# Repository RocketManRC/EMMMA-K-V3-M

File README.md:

# EMMMA-K-V3

# Introduction
The EMMMA-K is a MIDI controller for electronic music that uses touch pins for note keys and user interface. A motion sensor is used to generate MIDI commands for effects such as pitch bend and mod wheel.

The layout of the touch pins for note keys is modeled after the Kalimba (a.k.a. thumb piano) which is a modernized version of the MBira, an ancient African plucked string instrument.

The history and evolution of the MBira and Kalimba is given on Wikipedia here:

[https://en.wikipedia.org/wiki/Mbira](https://en.wikipedia.org/wiki/Mbira)

A great place to see and hear what the Kalimba is all about is April Yang's YouTube channel:

[https://www.youtube.com/channel/UCV0A2VeScCoxiMhsA2kiIKw](https://www.youtube.com/channel/UCV0A2VeScCoxiMhsA2kiIKw)

In January, 2020 I became interested in making an electronic version of the Kalimba because I wanted a keyboard for electronic music that wasn't piano based and also could be hand-held. In March of that year I started working on a proof-of-concept prototype which I called the EMMMA-K. A write-up of that project is on my website here:

[https://www.rocketmanrc.com/emmma-k.html](https://www.rocketmanrc.com/emmma-k.html)

As crude as that first prototype was it actually performed pretty well and so when the COVID-19 lockdown started I decided to spend the time on a second version that had a better shape and layout and would be easier to build. There is also a write-up of that project here:

[https://www.rocketmanrc.com/emmma-k-v2.html](https://www.rocketmanrc.com/emmma-k-v2.html)

This version supported additional music scales in addition to the Kalimba's C Major scale and a user interface was provided to change scale, key and octave.

Fast forward to October 2022... After working on a number of other unrelated projects I started researching what microcontrollers could be used to replace the TeensyLCs I was using that were no longer available due to the dreaded world-wide semiconductor shortage. The primary requirement was touch pin performance meaning good sensitivity and low latency. I discovered that the new ESP32-S2 and ESP32-S3 from Espressif are excellent for this purpose and so the EMMMA-K-V3 was born.

**Videos:**

[https://vimeo.com/858654116](https://vimeo.com/858654116) Introduction

[https://vimeo.com/858421865](https://vimeo.com/858421865) Overview of Features

[https://vimeo.com/858731197](https://vimeo.com/858731197) Under the Hood

# Features

- Kalimba style keyboard with highly responsive and low latency touch pins.
- USB-C connector for USB MIDI and/or power.
- Wireless MIDI over BLE (Bluetooth Low Energy) or ESP-Now wireless to a USB MIDI hub or a Serial MIDI hub.
- ESP-Now wireless is ultra low latency (approximately 1.5 milliseconds).
- Dedicated option touch pin on the right side to enable tilt sensor for pitch bend and mod wheel (or other CC command).
- Multipurpose option touch pin on the left side for switching between major and minor relative scales, changing to chord mode and disabling the adjacent pin and dissonant note filters.
- User interface with OLED display and dedicated touch pins.
- Change Octave, Key and Scale on the fly or display notes as played.
- Settings mode to enable or disable filters, change MIDI channel, set master volume, set CC for mod wheel and choose wireless mode.

# System Design

This is a dual microcontroller master/slave system with a ESP32-S3 used for the master and a ESP32-S2 (or S3) for the slave. Each microcontroller has 14 touch pins and the ESP32-S3 is required for the master to support wireless over BLE (the ESP32-S2 does not). The microcontrollers exchange pin data via a UART connection with the master polling the slave for synchronous communications. The baud rate is set to 2000000 baud to eliminate any noticable latency.

The motion sensor is a breakout board with a MPU-6050 IMU and is connected to the master via I2C. The board provides three absolute angle measurments (roll, pitch and yaw) using the internal processing of the MPU-6050. The roll axis is used for the mod wheel and the pitch axis is used for pitch bend. The yaw axis is not currently used but could be used for some other purpose.

The use of the motion sensor to generate effects is enabled by touching and holding the option pin on the right hand side of the enclosure. This does not require a note to be played which has the advantage of allowing the EMMMA-K to be used for effects along with another MIDI controller. It also has the advantage that the effects will still be applied to a note with sustain even if the noteoff MIDI command has been issued. When the option pin is touched centre angles are calculated for roll and pitch and then the effects are calculated relative to that those. The logic can be changed so that absolute angles are used which works just as well and is a matter of personal preference. Generation of the effects uses a concept from model aviation called "expo". This means that the change in value of the effects are reduced around around the centre position giving a much smoother response overall.

A OLED display of resolution of 128 by 64 pixels is used for the user interface along with three dedicated touch pins. This display is on a seperate I2C port.

Power for the system is provided by a USB connection to a USB power pack or computer USB port.

To minimize point to point wiring PCBs have been designed to carry both the Master and Slave microcontroller boards.

The microcontroller boards are the ESP32-S3-DevKitC-1 and ESP32-S2-DevKitC-1 from Espressif and are available from all the major component suppliers. Alternatively there are versions of the S3 dev board available from AliExpress.

The code for the slave processor (inspite of what Github says in the repository list and pins) is located here:

[https://github.com/RocketManRC/EMMMA-K-V3-S](https://github.com/RocketManRC/EMMMA-K-V3-S)

The code for the wireless hub is located here:

[https://github.com/RocketManRC/EMMMA-K-V3-W](https://github.com/RocketManRC/EMMMA-K-V3-S)

# Building

I've designed a 3D-printed case that has evolved quite a bit since the very first prototype. I've tried to make it as ergonomic as possible in terms of size and balance and spacing between touch pins. The STL files for 3D printing are here [STL](STL-Files).

It is not necessary to have the 3D-printed case to try out this system as something made of foam board from the Dollar store works just fine.

I do recommend getting the printed circuit boards however as it makes the wiring for the touch pins a lot easier and reproducable although hand wiring will work as well. I had my boards made at JLCPCB. 

The KiCAD 6 design files and the gerbers are here [PCBs](KiCAD).

### Wiring:

| Master MCU | Slave MCU |
| ---------- | --------- |
| GND        | GND       |
| 38         | TX        |
| 39         | RX        |

| Master MCU | MPU6050 |
| ---------- | ------- |
| GND        | GND     |
| 41         | SDA     |
| 42         | SCL     |
| 3.3V       | VCC     |

| Master MCU | OLED    |
| ---------- | ------- |
| GND        | GND     |
| 5V         | 5V      |
| 36         | SCL     |
| 35         | SDA     |

# Firmware

This is a PlatformIO project using the Arduino Framework. It might be possible to build the firmware using the Arduino IDE however this has not been tested as I don't use the Arduino IDE anymore.

Here is a short YouTube video that shows what is required to build and upload a PlatformIO project [https://www.youtube.com/watch?v=nlE2203Q3XI](https://www.youtube.com/watch?v=nlE2203Q3XI).

### Note: 

There is a quirk with the ESP32-S3 microcontroller that when a project uses USB MIDI the microcontroller must be put in bootloader mode before uploading new firmware otherwise there will be an error. This is not the case if USB MIDI is disabled. In platformio.ini you will see a comment telling how to enable and disable USB MIDI.

# User Guide

# User Interface Photos

### Main Menu:

### Settings:

# Reference Data

ESP32-S2-DevKitC-1: [https://docs.espressif.com/projects/esp-idf/en/latest/esp32s2/hw-reference/esp32s2/user-guide-s2-devkitc-1.html](https://docs.espressif.com/projects/esp-idf/en/latest/esp32s2/hw-reference/esp32s2/user-guide-s2-devkitc-1.html)

ESP32-S3-DevKitC-1: [https://docs.espressif.com/projects/esp-idf/en/latest/esp32s3/hw-reference/esp32s3/user-guide-devkitc-1.html](https://docs.espressif.com/projects/esp-idf/en/latest/esp32s3/hw-reference/esp32s3/user-guide-devkitc-1.html)

ESP32-S3-DevKitC-1 (N8R2 version) from AliExpress: [https://vi.aliexpress.com/item/1005004586894190.html](https://vi.aliexpress.com/item/1005004586894190.html)

USB-C Breakout Board from AliExpress: [https://vi.aliexpress.com/item/1005001337982060.html](https://vi.aliexpress.com/item/1005001337982060.html) Make sure to choose the female connector although having both may come in handy.

Schottky Diode: [https://www.digikey.ca/en/products/detail/panjit-international-inc/SS1040L-R1-00001/14660138](https://www.digikey.ca/en/products/detail/panjit-international-inc/SS1040L-R1-00001/14660138)

Upholstery Nails (for touch pins): [https://www.amazon.ca/Upholstery-Vintage-Furniture-Upholster-Decorative/dp/B08Q7XC9Y1](https://www.amazon.ca/Upholstery-Vintage-Furniture-Upholster-Decorative/dp/B08Q7XC9Y1)

ABS Glue: [https://a.co/d/97ip9cB](https://a.co/d/97ip9cB) I purchased this locally at the hardware store.

Nylon Standoffs and screws: [https://a.co/d/cQluBSF](https://a.co/d/cQluBSF)

M5 Stack OLED Display: [https://vi.aliexpress.com/item/1005003297480376.html](https://vi.aliexpress.com/item/1005003297480376.html) I bought mine from DigiKey for less but at the moment (September 14, 2023) they only have 2 left in stock

MPU-6050 Breakout Board: [https://a.co/d/5xTt3AK](https://a.co/d/5xTt3AK)

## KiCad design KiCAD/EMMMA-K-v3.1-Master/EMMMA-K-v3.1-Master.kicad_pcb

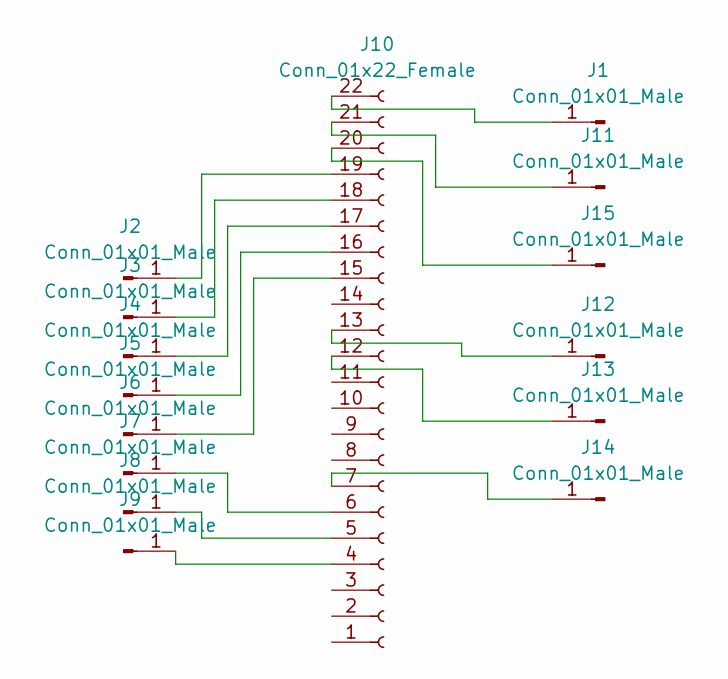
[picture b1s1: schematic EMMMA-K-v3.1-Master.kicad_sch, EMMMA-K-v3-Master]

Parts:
J1, J11, J12, J13, J14, J15: Conn_01x01_Male; SolderWire-1.5sqmm_1x01_D1.0mm_OD3mm
J2, J3, J4, J5, J6, J7, J8, J9: Conn_01x01_Male; SolderWire-EMMMA-3mm1.7mm
J10: Conn_01x22_Female; PinHeader_1x22_P2.54mm_Vertical

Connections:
unnamed: J1.1, J10.22
unnamed: J9.1, J10.4
unnamed: J8.1, J10.5
unnamed: J7.1, J10.6
unnamed: J10.7, J14.1
unnamed: J10.12, J13.1
unnamed: J10.13, J12.1
unnamed: J6.1, J10.15
unnamed: J5.1, J10.16
unnamed: J4.1, J10.17
unnamed: J3.1, J10.18
unnamed: J2.1, J10.19
unnamed: J10.20, J15.1
unnamed: J10.21, J11.1

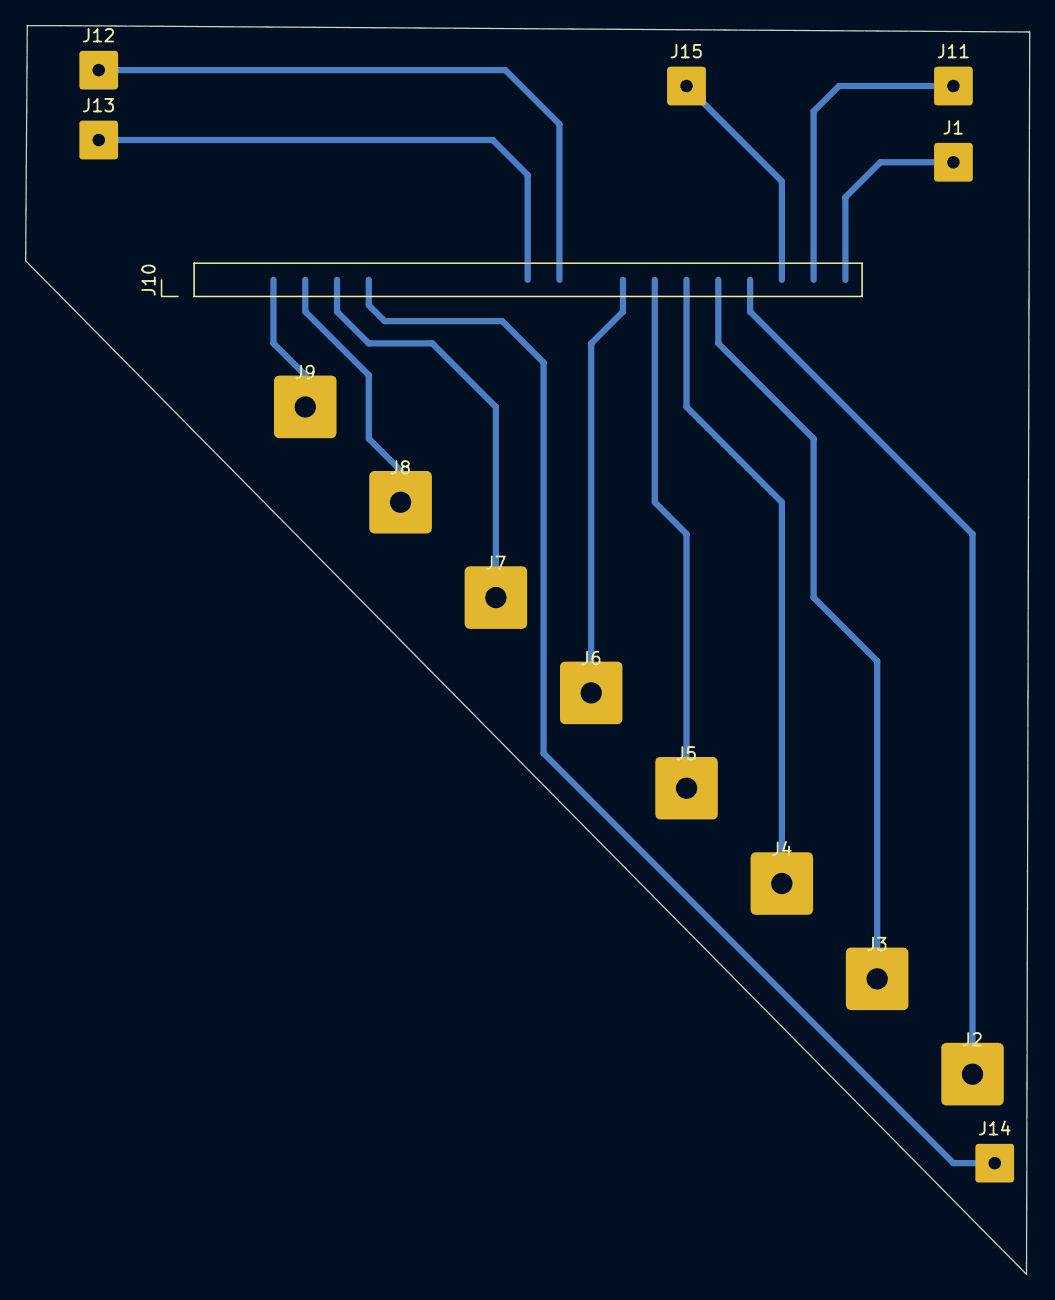
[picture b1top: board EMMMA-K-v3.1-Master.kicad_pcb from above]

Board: 2 copper layers, 80.3 x 99.8 mm, 15 parts (0 on the bottom side), 14 nets.

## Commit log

2023-08-09 Cleanup platformio.ini
2023-08-09 Start on README.md
2023-08-14 Added patchfile.py to patch the MIDI LIbrary to fix pitch bend and also updated the readme
2023-08-14 Update readme plus add STL and PCB files
2023-08-15 Fix image names
2023-08-15 Update README.md
    Fix external links
2023-09-13 Create LICENSE
    Apache License Version 2.0
2023-09-13 Add PCB files and major cleanup of main.cpp
2023-09-14 More source code cleanup
2023-09-14 Update README.md
    Added tables for wiring components together
2023-10-15 Update main.cpp
    Add changeMidiChannel() to incoming messages
